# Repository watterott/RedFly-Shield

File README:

RedFly-Shield
-------------
WiFi/WLAN Shield for Arduino
http://www.watterott.com/en/Arduino-RedFly-Shield

More information in the wiki: https://github.com/watterott/RedFly-Shield/wiki

Directories:
 /fw  - Firmware for the WiFi module
 /pcb - Schematics and Layout files
 /src - Arduino Library and Examples

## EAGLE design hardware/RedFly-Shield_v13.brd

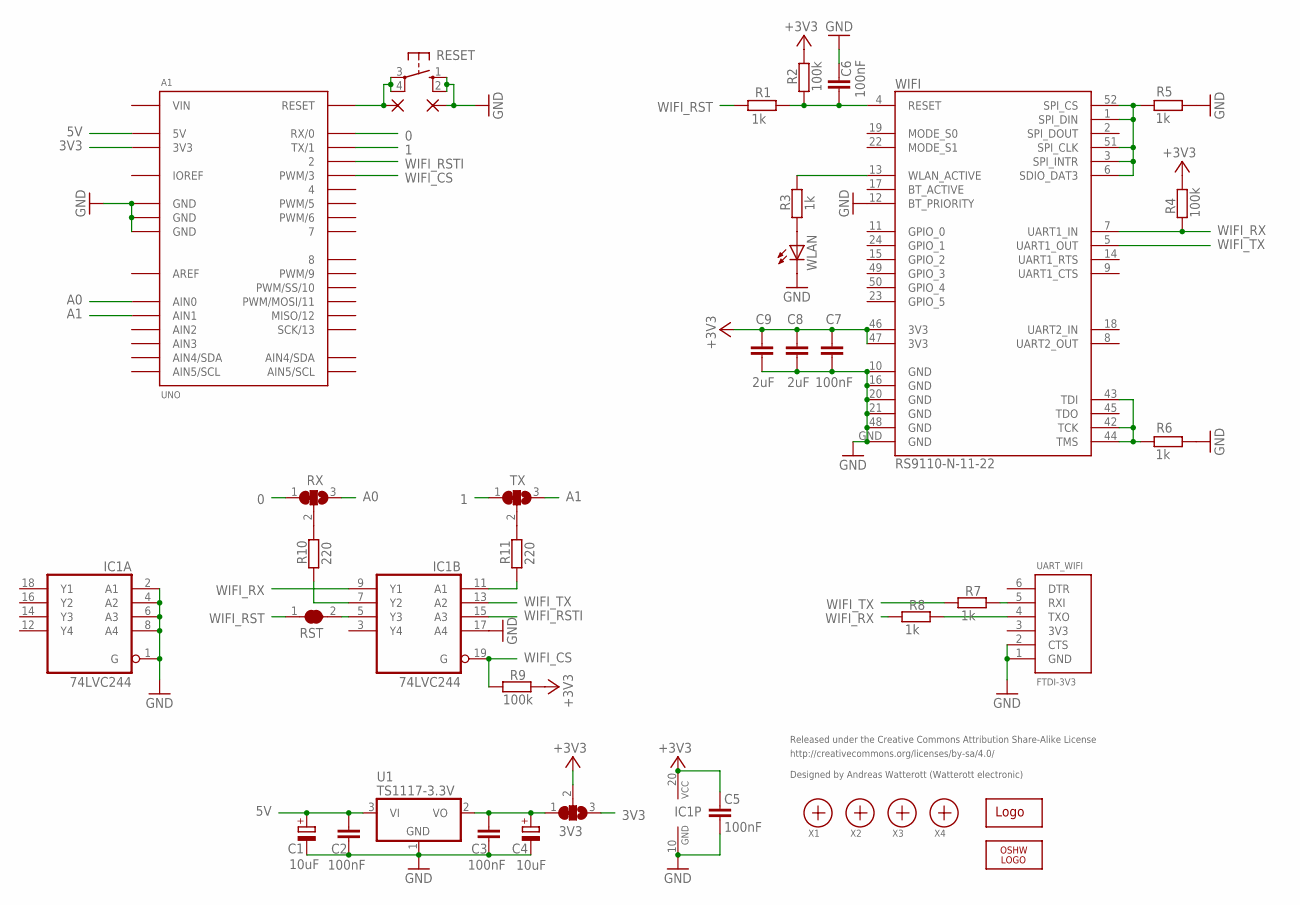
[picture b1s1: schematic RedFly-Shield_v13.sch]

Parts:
3V3: SJ2W; SJ_2
A1: UNO
C1, C4: 10uF; 153CLV-0505
C2, C3, C5, C6, C7: 100nF; C0603
C8, C9: 2uF; C0603
GND: SMD2; SMD1,27-2,54
IC1: 74LVC244; SO20W
LOGO1: OSHW_LOGO_6MILX0100-NT; OSHW_6X100_NOTEXT
R1, R3, R5, R6, R7, R8: 1k; R0603
R2, R4, R9: 100k; R0603
R10, R11: 220; R0603
RESET: 10-XX; B3F-10XX
RST: SJ
RST2: SMD2; SMD1,27-2,54
RX: SJ2W; SJ_2
TX: SJ2W; SJ_2
U1: TS1117-3.3V; SOT223
U$1: WE-LOGO
UART_WIFI: FTDI-3V3; FTDI
WIFI: RS9110-N-11-22; RS9110-N-11-21
WLAN: LEDCHIPLED_0603; CHIPLED_0603
X1, X2, X3, X4: PASSER

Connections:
0: A1.0 (RX/0), RX.1
1: A1.1 (TX/1), TX.1
3V3: 3V3.3, A1.3V3
3V_OUT: 3V3.1, C3.1, C4.+, U1.2 (VO)
5V: A1.5V, C1.+, C2.1, U1.3 (VI)
+3V3: 3V3.2, C5.1, C7.1, C8.1, C9.1, IC1.20 (VCC), R2.2, R4.1, R9.2, WIFI.46 (3V3), WIFI.47 (3V3)
A0: A1.AIN0, RX.3
A1: A1.AIN1, TX.3
AREF: A1.AREF
GND: A1.GND@1 (GND), A1.GND@2 (GND), A1.GND@3 (GND), C1.-, C2.2, C3.2, C4.-, C5.2, C6.1, C7.2, C8.2, C9.2, GND.1, IC1.1 (G), IC1.2 (A1), IC1.4 (A2), IC1.6 (A3), IC1.8 (A4), IC1.10 (GND), IC1.17 (A4), R5.1, R6.1, RESET.1 (S), RESET.2 (S1), U1.1 (GND), UART_WIFI.1 (GND), UART_WIFI.2 (CTS), WIFI.10 (GND), WIFI.12 (BT_PRIORITY), WIFI.16 (GND), WIFI.20 (GND), WIFI.21 (GND), WIFI.48 (GND), WIFI.GND, WLAN.C
IOREF: A1.IOREF
unnamed: R6.2, WIFI.42 (TCK), WIFI.43 (TDI), WIFI.44 (TMS)
unnamed: R5.2, WIFI.1 (SPI_DIN), WIFI.3 (SPI_INTR), WIFI.6 (SDIO_DAT3), WIFI.51 (SPI_CLK), WIFI.52 (SPI_CS)
unnamed: R3.1, WIFI.13 (WLAN_ACTIVE)
unnamed: R3.2, WLAN.A
unnamed: R7.1, UART_WIFI.5 (RXI)
unnamed: R8.1, UART_WIFI.4 (TXO)
RST: A1.RST (RESET), RESET.3, RESET.4 (P1), RST2.1
VIN: A1.VIN
WIFI_CS: A1.3 (PWM/3), IC1.19 (G), R9.1
WIFI_RST: R1.2, RST.1
WIFI_RST2: C6.2, R1.1, R2.1, WIFI.4 (RESET)
WIFI_RSTI: A1.2, IC1.15 (A3)
WIFI_RSTO: IC1.5 (Y3), RST.2
WIFI_RX: IC1.9 (Y1), R4.2, R8.2, WIFI.7 (UART1_IN)
WIFI_RX2: R11.1, TX.2
WIFI_RXI: IC1.11 (A1), R11.2
WIFI_TX: IC1.13 (A2), R7.2, WIFI.5 (UART1_OUT)
WIFI_TX2: R10.2, RX.2
WIFI_TXO: IC1.7 (Y2), R10.1

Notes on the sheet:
Released under the Creative Commons Attribution Share-Alike License
http://creativecommons.org/licenses/by-sa/4.0/
Designed by Andreas Watterott (Watterott electronic)

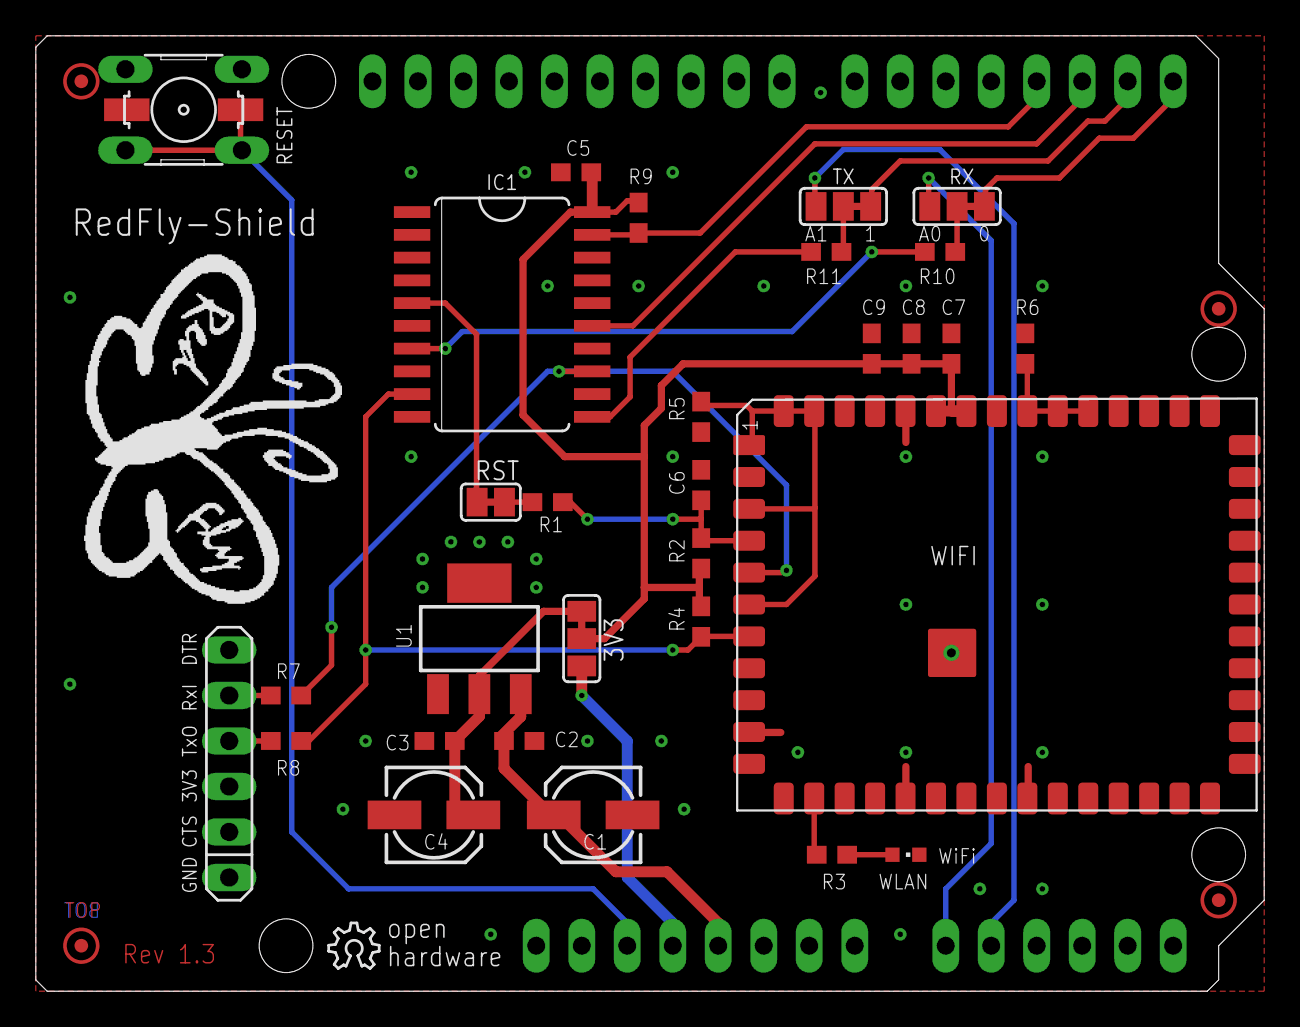
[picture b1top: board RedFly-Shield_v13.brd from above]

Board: 2 copper layers, 68.6 x 53.3 mm, 39 parts (1 on the bottom side), 27 nets.

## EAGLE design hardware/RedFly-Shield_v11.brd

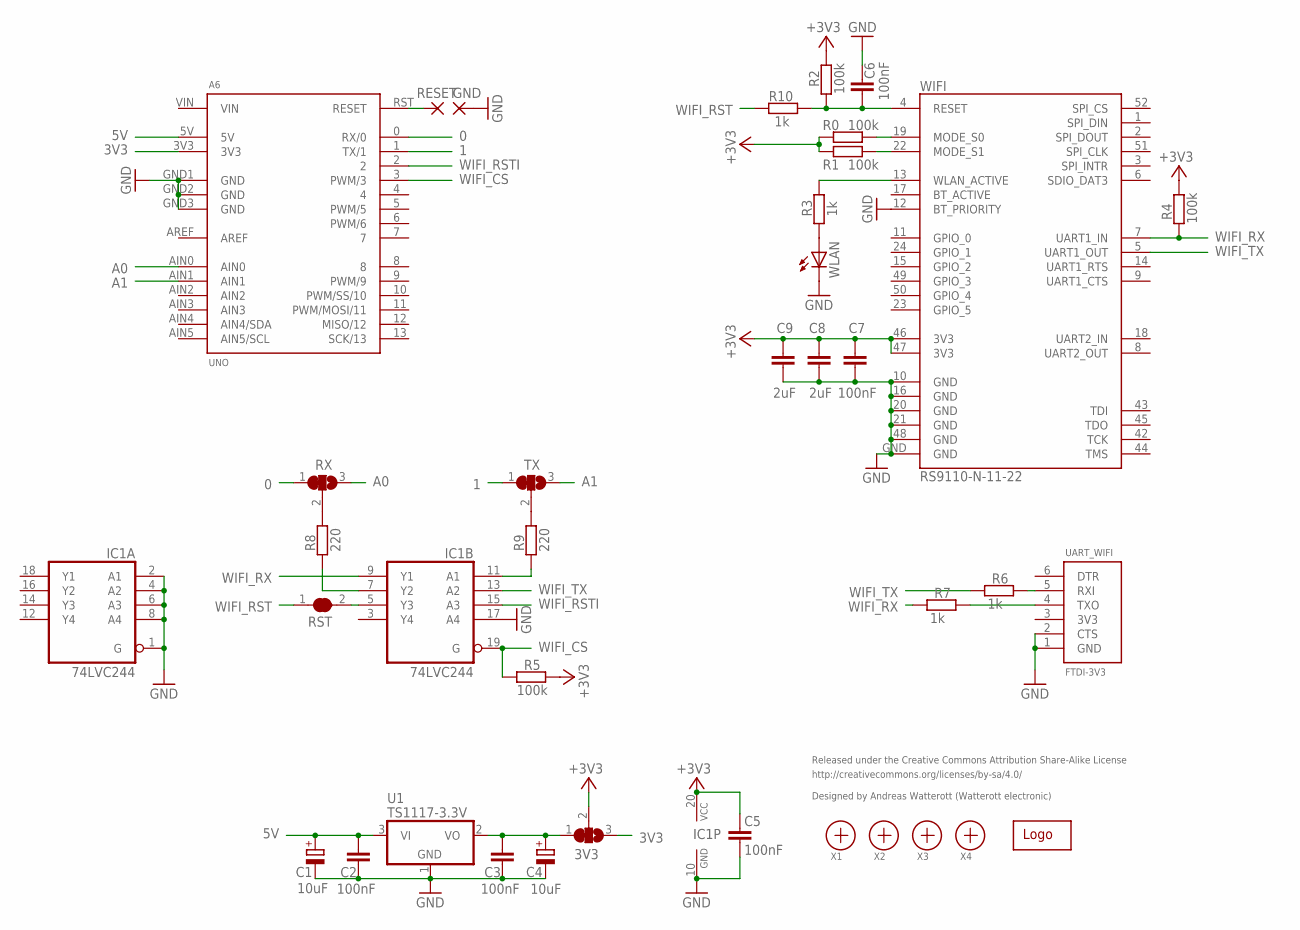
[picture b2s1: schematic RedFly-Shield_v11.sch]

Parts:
3V3: SJ2W; SJ_2
A6: UNO; DUEMILANOVE
C1, C4: 10uF; 153CLV-0505
C2, C3, C5, C6, C7: 100nF; C0603
C8, C9: 2uF; C0603
GND: SMD2; SMD1,27-2,54
IC1: 74LVC244; SO20W
R0, R1, R2, R4, R5: 100k; R0603
R3, R6, R7, R10: 1k; R0603
R8, R9: 220; R0603
RESET: SMD2; SMD1,27-2,54
RST: SJ
RX: SJ2W; SJ_2
TX: SJ2W; SJ_2
U1: TS1117-3.3V; SOT223
U$1: WE-LOGO
UART_WIFI: FTDI-3V3; FTDI
WIFI: RS9110-N-11-22; RS9110-N-11-21
WLAN: LEDCHIPLED_0805; CHIPLED_0805
X1, X2, X3, X4: PASSER

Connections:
0: A6.0 (RX/0), RX.1
1: A6.1 (TX/1), TX.1
3V3: 3V3.3, A6.3V3
3V_OUT: 3V3.1, C3.1, C4.+, U1.2 (VO)
5V: A6.5V, C1.+, C2.1, U1.3 (VI)
+3V3: 3V3.2, C5.1, C7.1, C8.1, C9.1, IC1.20 (VCC), R0.2, R1.2, R2.2, R4.1, R5.2, WIFI.46 (3V3), WIFI.47 (3V3)
A0: A6.AIN0, RX.3
A1: A6.AIN1, TX.3
AREF: A6.AREF
GND: A6.GND1 (GND), A6.GND2 (GND), A6.GND3 (GND), C1.-, C2.2, C3.2, C4.-, C5.2, C6.1, C7.2, C8.2, C9.2, GND.1, IC1.1 (G), IC1.2 (A1), IC1.4 (A2), IC1.6 (A3), IC1.8 (A4), IC1.10 (GND), IC1.17 (A4), U1.1 (GND), UART_WIFI.1 (GND), UART_WIFI.2 (CTS), WIFI.10 (GND), WIFI.12 (BT_PRIORITY), WIFI.16 (GND), WIFI.20 (GND), WIFI.21 (GND), WIFI.48 (GND), WIFI.GND, WLAN.C
unnamed: R0.1, WIFI.19 (MODE_S0)
unnamed: R1.1, WIFI.22 (MODE_S1)
unnamed: R3.1, WIFI.13 (WLAN_ACTIVE)
unnamed: R3.2, WLAN.A
unnamed: R6.1, UART_WIFI.5 (RXI)
unnamed: R7.1, UART_WIFI.4 (TXO)
RST: A6.RST (RESET), RESET.1
VIN: A6.VIN
WIFI_CS: A6.3 (PWM/3), IC1.19 (G), R5.1
WIFI_RST: R10.2, RST.1
WIFI_RST2: C6.2, R2.1, R10.1, WIFI.4 (RESET)
WIFI_RSTI: A6.2, IC1.15 (A3)
WIFI_RSTO: IC1.5 (Y3), RST.2
WIFI_RX: IC1.9 (Y1), R4.2, R7.2, WIFI.7 (UART1_IN)
WIFI_RX2: R9.1, TX.2
WIFI_RXI: IC1.11 (A1), R9.2
WIFI_TX: IC1.13 (A2), R6.2, WIFI.5 (UART1_OUT)
WIFI_TX2: R8.2, RX.2
WIFI_TXO: IC1.7 (Y2), R8.1

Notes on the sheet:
Released under the Creative Commons Attribution Share-Alike License
http://creativecommons.org/licenses/by-sa/4.0/
Designed by Andreas Watterott (Watterott electronic)

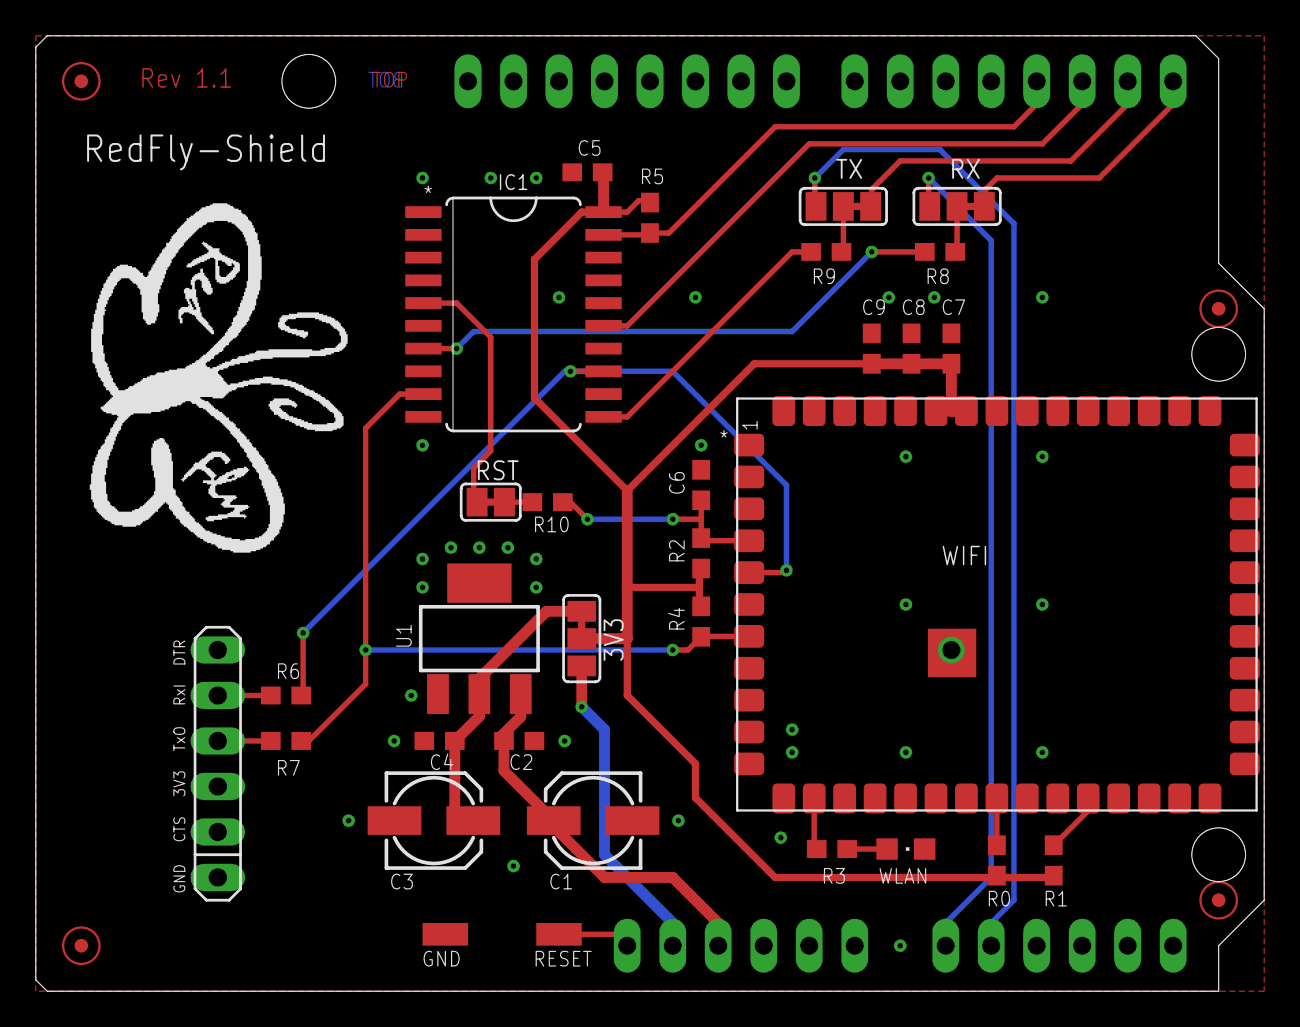
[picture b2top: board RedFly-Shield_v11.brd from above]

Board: 2 copper layers, 68.6 x 53.3 mm, 37 parts (1 on the bottom side), 27 nets.

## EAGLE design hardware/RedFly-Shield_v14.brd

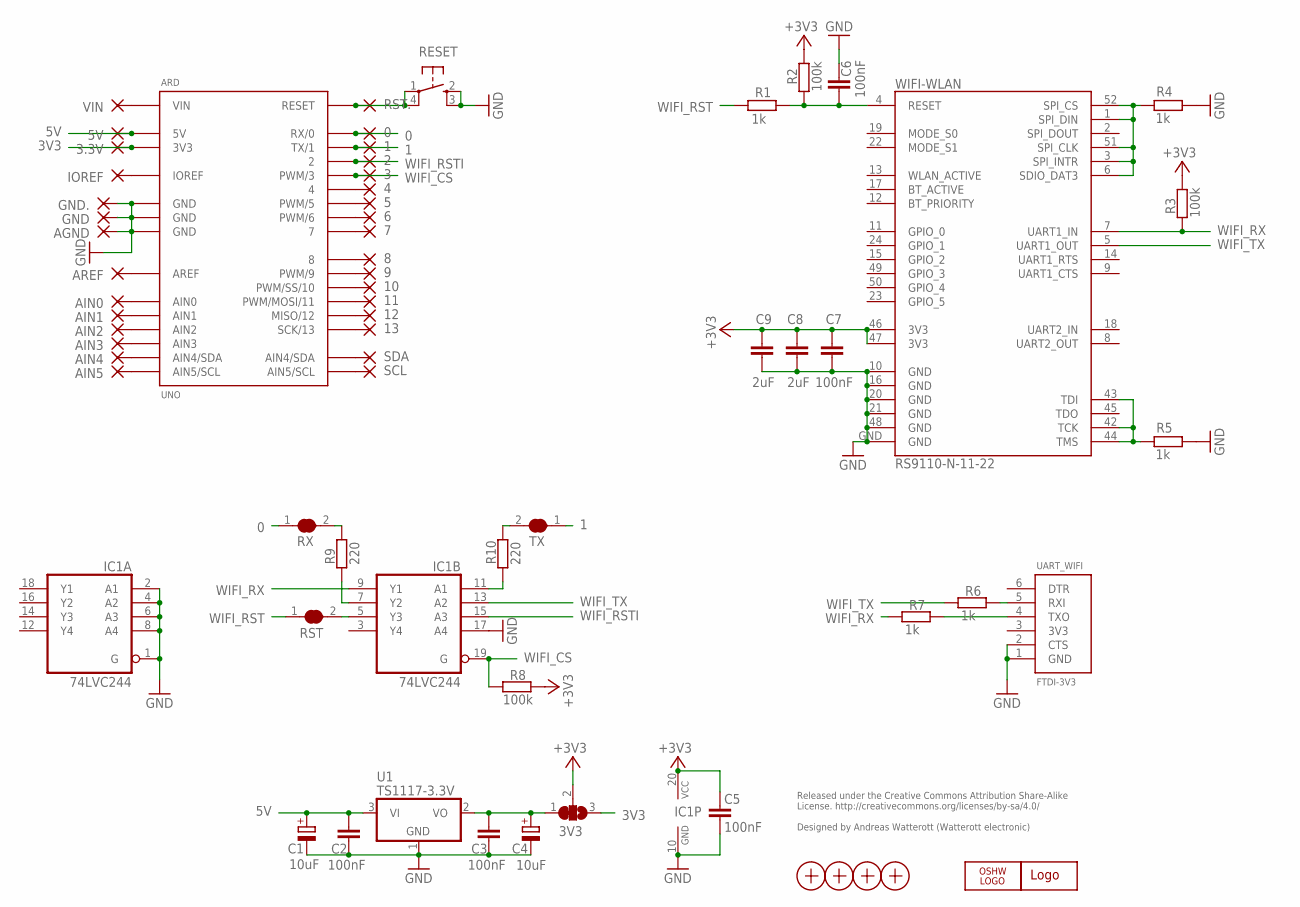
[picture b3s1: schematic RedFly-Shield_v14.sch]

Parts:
0, 1, 2, 3, 3.3V, 4, 5, 5V, 6, 7, 8, 9, 10, 11, 12, 13: WIREPAD1,6/0,8; 1,6/0,8
3V3: SJ2W; SJ_2
AGND: WIREPAD1,6/0,8; 1,6/0,8
AIN0, AIN1, AIN2, AIN3, AIN4, AIN5: WIREPAD1,6/0,8; 1,6/0,8
ARD: UNO
AREF: WIREPAD1,6/0,8; 1,6/0,8
C1, C4: 10uF; 153CLV-0505
C2, C3, C5, C6, C7: 100nF; C0603
C8, C9: 2uF; C0603
GND, GND.: WIREPAD1,6/0,8; 1,6/0,8
IC1: 74LVC244; SO20W
IOREF: WIREPAD1,6/0,8; 1,6/0,8
LOGO1: WE-LOGO
LOGO2: OSHW_LOGO_6MILX0100-NT; OSHW_6X100_NOTEXT
R1, R4, R5, R6, R7: 1k; R0603
R2, R3, R8: 100k; R0603
R9, R10: 220; R0603
RESET: SW_SMDS; SW_SMD4@1
RST: SJ
RST.: WIREPAD1,6/0,8; 1,6/0,8
RX: SJ
SCL: WIREPAD1,6/0,8; 1,6/0,8
SDA: WIREPAD1,6/0,8; 1,6/0,8
TX: SJ
U1: TS1117-3.3V; SOT223
UART_WIFI: FTDI-3V3; FTDI
VIN: WIREPAD1,6/0,8; 1,6/0,8
WIFI-WLAN: RS9110-N-11-22; RS9110-N-11-21
X1, X2, X3, X4: PASSER

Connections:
0: 0.1, ARD.0 (RX/0), RX.1
1: 1.1, ARD.1 (TX/1), TX.1
3V3: 3.3V.1, 3V3.3, ARD.3V3
3V_OUT: 3V3.1, C3.1, C4.+, U1.2 (VO)
5V: 5V.1, ARD.5V, C1.+, C2.1, U1.3 (VI)
+3V3: 3V3.2, C5.1, C7.1, C8.1, C9.1, IC1.20 (VCC), R2.2, R3.1, R8.2, WIFI-WLAN.46 (3V3), WIFI-WLAN.47 (3V3)
A0: AIN0.1, ARD.AIN0
A1: AIN1.1, ARD.AIN1
AREF: ARD.AREF, AREF.1
GND: AGND.1, ARD.GND@1 (GND), ARD.GND@2 (GND), ARD.GND@3 (GND), C1.-, C2.2, C3.2, C4.-, C5.2, C6.1, C7.2, C8.2, C9.2, GND.1, GND..1, IC1.1 (G), IC1.2 (A1), IC1.4 (A2), IC1.6 (A3), IC1.8 (A4), IC1.10 (GND), IC1.17 (A4), R4.1, R5.1, RESET.2 (S), RESET.3 (S1), U1.1 (GND), UART_WIFI.1 (GND), UART_WIFI.2 (CTS), WIFI-WLAN.10 (GND), WIFI-WLAN.16 (GND), WIFI-WLAN.20 (GND), WIFI-WLAN.21 (GND), WIFI-WLAN.48 (GND), WIFI-WLAN.GND
IOREF: ARD.IOREF, IOREF.1
unnamed: ARD.SCL (AIN5/SCL), SCL.1
unnamed: R5.2, WIFI-WLAN.42 (TCK), WIFI-WLAN.43 (TDI), WIFI-WLAN.44 (TMS)
unnamed: ARD.SDA (AIN4/SDA), SDA.1
unnamed: R4.2, WIFI-WLAN.1 (SPI_DIN), WIFI-WLAN.3 (SPI_INTR), WIFI-WLAN.6 (SDIO_DAT3), WIFI-WLAN.51 (SPI_CLK), WIFI-WLAN.52 (SPI_CS)
unnamed: 4.1, ARD.4
unnamed: 5.1, ARD.5 (PWM/5)
unnamed: 6.1, ARD.6 (PWM/6)
unnamed: 7.1, ARD.7
unnamed: 8.1, ARD.8
unnamed: 9.1, ARD.9 (PWM/9)
unnamed: 10.1, ARD.10 (PWM/SS/10)
unnamed: 11.1, ARD.11 (PWM/MOSI/11)
unnamed: 12.1, ARD.12 (MISO/12)
unnamed: 13.1, ARD.13 (SCK/13)
unnamed: AIN2.1, ARD.AIN2
unnamed: AIN3.1, ARD.AIN3
unnamed: AIN4.1, ARD.AIN4 (AIN4/SDA)
unnamed: AIN5.1, ARD.AIN5 (AIN5/SCL)
unnamed: R6.1, UART_WIFI.5 (RXI)
unnamed: R7.1, UART_WIFI.4 (TXO)
RST: ARD.RST (RESET), RESET.1, RESET.4 (P1), RST..1
VIN: ARD.VIN, VIN.1
WIFI_CS: 3.1, ARD.3 (PWM/3), IC1.19 (G), R8.1
WIFI_RST: R1.2, RST.1
WIFI_RST2: C6.2, R1.1, R2.1, WIFI-WLAN.4 (RESET)
WIFI_RSTI: 2.1, ARD.2, IC1.15 (A3)
WIFI_RSTO: IC1.5 (Y3), RST.2
WIFI_RX: IC1.9 (Y1), R3.2, R7.2, WIFI-WLAN.7 (UART1_IN)
WIFI_RX2: R10.1, TX.2
WIFI_RXI: IC1.11 (A1), R10.2
WIFI_TX: IC1.13 (A2), R6.2, WIFI-WLAN.5 (UART1_OUT)
WIFI_TX2: R9.2, RX.2
WIFI_TXO: IC1.7 (Y2), R9.1

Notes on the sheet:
Released under the Creative Commons Attribution Share-Alike License. http://creativecommons.org/licenses/by-sa/4.0/ Designed by Andreas Watterott (Watterott electronic)

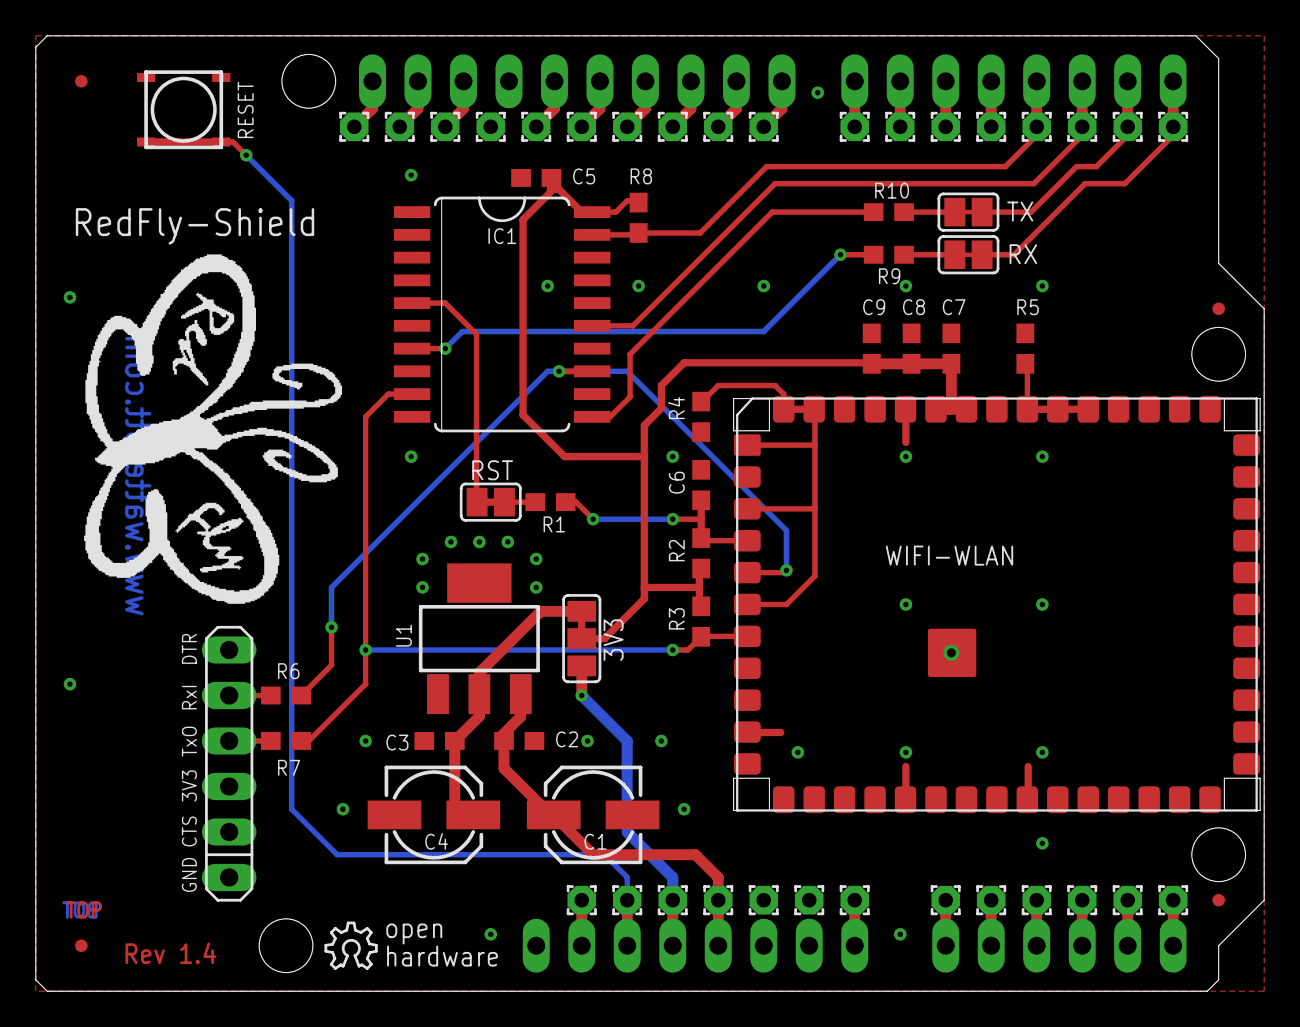
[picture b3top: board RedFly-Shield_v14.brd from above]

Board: 2 copper layers, 68.6 x 53.3 mm, 66 parts (1 on the bottom side), 44 nets.

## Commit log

2012-03-06 added layout files
2012-03-06 added fw files
2012-03-06 Lib v0.10
2012-03-06 Lib v0.11
2012-03-06 socketClose() now clears the input buffer.
2012-03-06 FW update guide now in the wiki
2012-03-06 updated readme's
2012-03-10 updated docu
2012-03-14 NBNS service bugfix
2012-03-14 nextscan only when network found
2012-03-20 socketClose(): close socket in WiFi module at first
2012-03-20 code clean up add socketClose() retry
2012-04-07 release v0.12
2012-04-13 bugfix in scan()
2012-04-17 FW update
2012-05-23 updated examples and docu
2012-05-31 new directory struct
2012-06-05 bugfix in socketListen()
2012-06-27 update docu
2012-07-12 code clean-up
2012-07-27 getversion(), getmac(), getip() now return error codes
2012-07-31 release v0.14
2012-08-02 added Arduino Leonardo support
2012-08-02 updated readme and hw diagram
2012-08-21 release v0.15
2012-08-21 image updated
2012-08-23 added selectable data rates on join().
2012-08-24 added more data rates updated docu
2012-09-07 updated docu+readme
2012-10-22 Added Cosm example.
2012-10-30 Updated ArdOSC examples (Leonardo support)
2012-11-26 updated schematics
2013-01-28 updated docu added ad-hoc example
2013-01-28 updated AdhocTest example
2013-01-28 updated AdhocTest example added InfrastructureTest example
2013-01-28 release v0.16
2013-02-09 code clean-up added project list
2013-03-11 updated readme and projects
2013-06-02 added new firmware v4.7.1
2013-06-02 changed docu format
2013-06-02 renamed cosm to xively
2013-06-02 rewrote timeout functions to be more portable
2013-07-31 updated examples + minor changes
2013-07-31 added v1.4 schematics+layout
2013-08-01 improved TwitterWriter example
2013-09-21 updated hardware diagram
2013-09-27 updated examples
2013-10-01 updated projects
2013-10-09 updated readme and docu
2014-01-02 moved examples to Arduino-Libs repository
2014-03-10 updated license infos
2014-08-21 updated layout and schematics
2014-11-07 cleaned up schematics and layout
2015-01-11 moved image
2015-07-25 removed projects
2015-08-21 changed path structure
2016-02-18 Updated keystroke
    The needed keystroke to go back is more complicated than `CTRL+C`
